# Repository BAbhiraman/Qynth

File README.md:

# DIY Synthesizer using the STM32F407G-DISC1 board
[Working slides](https://docs.google.com/presentation/d/1uzVbpTlb4Z4Ckb4epo5yxM_shybulsgjehzmY5z12NE/edit?usp=sharing)

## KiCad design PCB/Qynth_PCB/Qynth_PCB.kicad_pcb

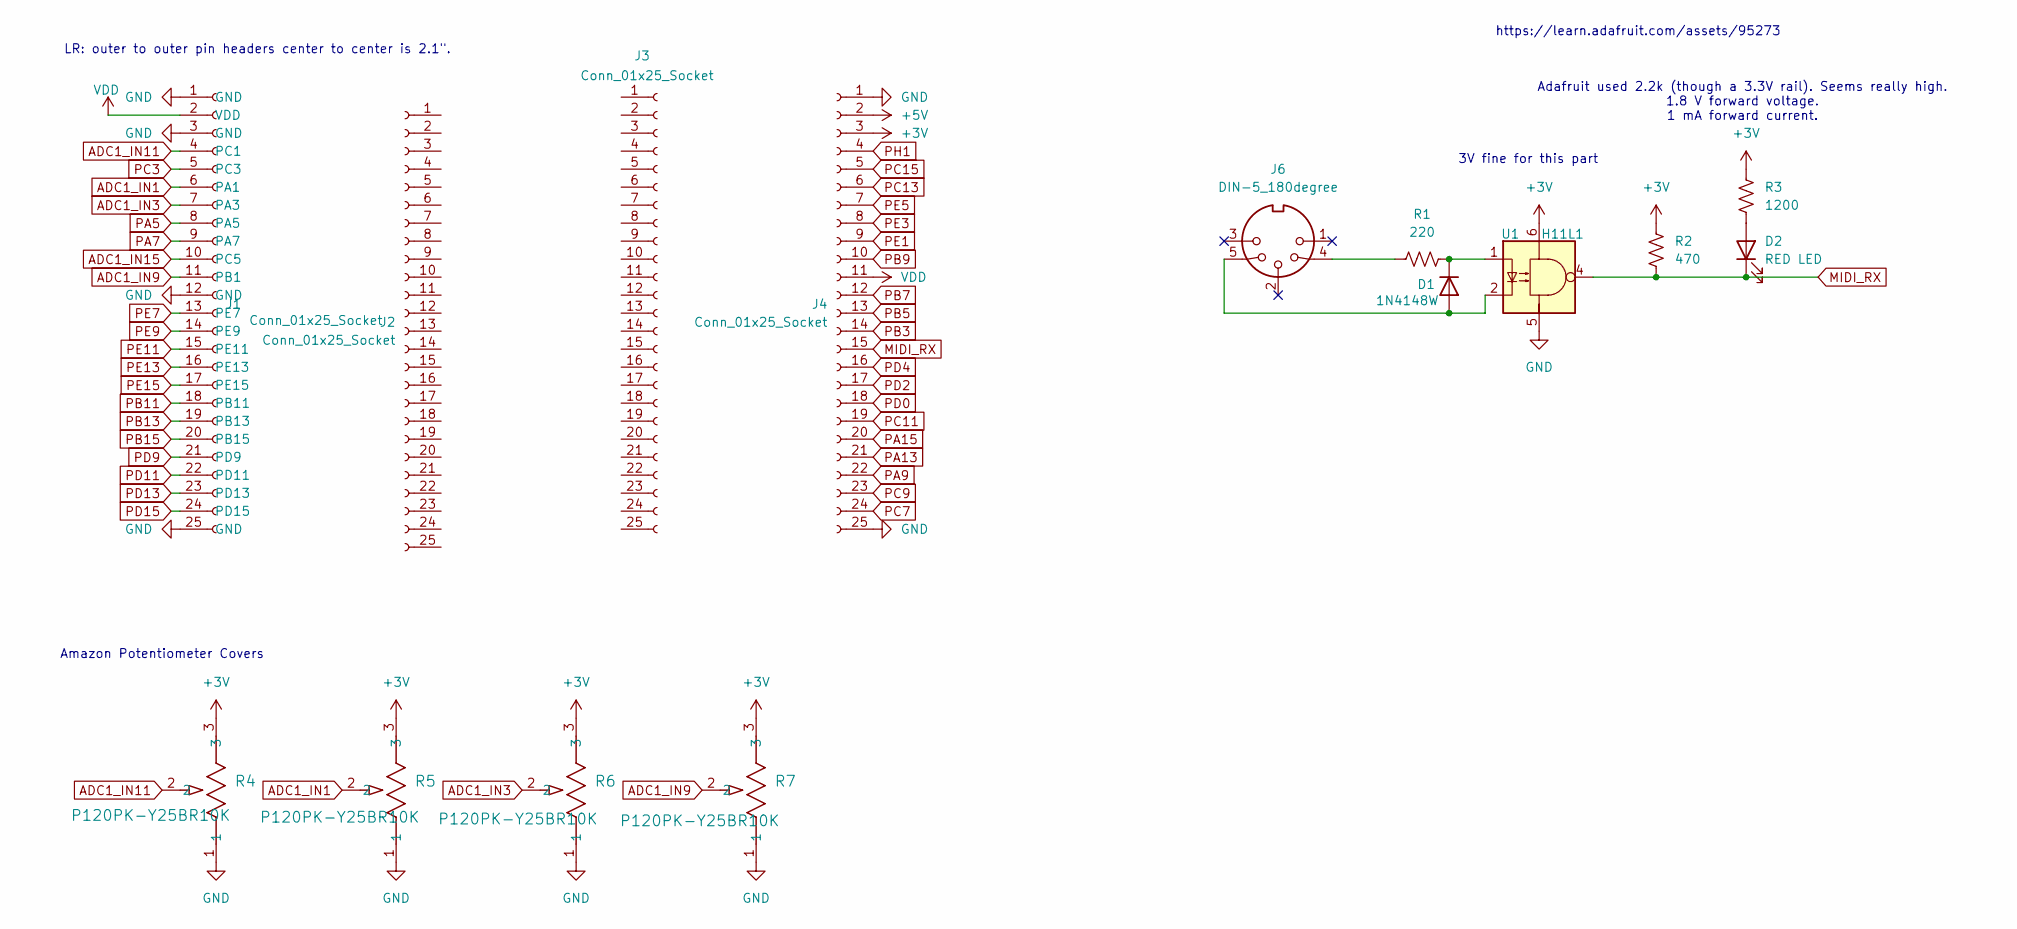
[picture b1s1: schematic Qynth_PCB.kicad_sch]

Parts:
D1: 1N4148W; D_SOD-123
D2: RED LED; LED_0402_1005Metric
J1, J2, J3, J4: Conn_01x25_Socket; PinSocket_1x25_P2.54mm_Vertical
J6: DIN-5_180degree; CUI_SDS-50J
R1: 220; R_0805_2012Metric_Pad1.20x1.40mm_HandSolder
R2: 470; R_0805_2012Metric
R3: 1200; R_0805_2012Metric
R4, R5, R6, R7: P120PK-Y25BR10K; POT_P120PK-x25_TTE
U1: H11L1; SMDIP-6_W7.62mm

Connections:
+3V: J4.3 (3V), R2.2, R3.2, R4.3, R5.3, R6.3, R7.3, U1.6
+5V: J4.2 (5V)
ADC1_IN1: J1.6 (PA1), R5.2
ADC1_IN3: J1.7 (PA3), R6.2
ADC1_IN9: J1.11 (PB1), R7.2
ADC1_IN11: J1.4 (PC1), R4.2
ADC1_IN15: J1.10 (PC5)
GND: J1.1 (GND), J1.3 (GND), J1.12 (GND), J1.25 (GND), J4.1 (GND), J4.25 (GND), R4.1, R5.1, R6.1, R7.1, U1.5
MIDI_RX: D2.1 (K), J4.15 (MIDI_RX), R2.1, U1.4
unnamed: D1.2 (A), J6.5, U1.2
unnamed: D1.1 (K), R1.2, U1.1
unnamed: D2.2 (A), R3.1
unnamed: J6.4, R1.1
PA5: J1.8 (PA5)
PA7: J1.9 (PA7)
PA9: J4.22 (PA9)
PA13: J4.21 (PA13)
PA15: J4.20 (PA15)
PB3: J4.14 (PB3)
PB5: J4.13 (PB5)
PB7: J4.12 (PB7)
PB9: J4.10 (PB9)
PB11: J1.18 (PB11)
PB13: J1.19 (PB13)
PB15: J1.20 (PB15)
PC3: J1.5 (PC3)
PC7: J4.24 (PC7)
PC9: J4.23 (PC9)
PC11: J4.19 (PC11)
PC13: J4.6 (PC13)
PC15: J4.5 (PC15)
PD0: J4.18 (PD0)
PD2: J4.17 (PD2)
PD4: J4.16 (PD4)
PD9: J1.21 (PD9)
PD11: J1.22 (PD11)
PD13: J1.23 (PD13)
PD15: J1.24 (PD15)
PE1: J4.9 (PE1)
PE3: J4.8 (PE3)
PE5: J4.7 (PE5)
PE7: J1.13 (PE7)
PE9: J1.14 (PE9)
PE11: J1.15 (PE11)
PE13: J1.16 (PE13)
PE15: J1.17 (PE15)
PH1: J4.4 (PH1)
VDD: J1.2 (VDD), J4.11 (VDD)

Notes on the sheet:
Amazon Potentiometer Covers
LR: outer to outer pin headers center to center is 2.1".
https://learn.adafruit.com/assets/95273
3V fine for this part
Adafruit used 2.2k (though a 3.3V rail). Seems really high. 1.8 V forward voltage. 1 mA forward current.

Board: 2 copper layers, 15 parts (0 on the bottom side), 12 nets, no tracks yet.

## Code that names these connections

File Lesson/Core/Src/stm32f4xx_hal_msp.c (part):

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    __HAL_RCC_GPIOA_CLK_ENABLE();
    __HAL_RCC_GPIOB_CLK_ENABLE();
    /**ADC1 GPIO Configuration
    PC1     ------> ADC1_IN11
    PC2     ------> ADC1_IN12
    PA1     ------> ADC1_IN1
    PA3     ------> ADC1_IN3
    PC4     ------> ADC1_IN14
    PB0     ------> ADC1_IN8
    PB1     ------> ADC1_IN9
    */
    GPIO_InitStruct.Pin = GPIO_PIN_1|GPIO_PIN_2|GPIO_PIN_4;
    GPIO_InitStruct.Mode = GPIO_MODE_ANALOG;
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    __HAL_RCC_ADC1_CLK_DISABLE();

    /**ADC1 GPIO Configuration
    PC1     ------> ADC1_IN11
    PC2     ------> ADC1_IN12
    PA1     ------> ADC1_IN1
    PA3     ------> ADC1_IN3
    PC4     ------> ADC1_IN14
    PB0     ------> ADC1_IN8
    PB1     ------> ADC1_IN9
    */
    HAL_GPIO_DeInit(GPIOC, GPIO_PIN_1|GPIO_PIN_2|GPIO_PIN_4);

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
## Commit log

2025-03-21 got ping from ext DAC
2025-03-22 heard some sound!
2025-03-22 DMA I2S working but clicking persists
2025-03-22 what the fuck? kinda cool though.
2025-03-22 ok this doesn't have buzzing, very sensitive though
2025-03-23 working through double buffering issues, ode to joy.
2025-03-23 fixed volatile thing by using loop variable. Keep an eye on this issue.
2025-03-23 MAJOR DAJOR progress.
    Got rid of clicking artifacts. Ctrler spent all its time calculating sine and barely finished on time. New logic uses sine lookup table.
    TODO put flag logic back to previous state.
2025-03-27 restoring old double buffering logic. prototyping serial over USB.
2025-04-02 got midi_input_test to compile with files from internet
2025-04-02 Made substitutions recommended by hackaday.io. Compiled.
2025-04-04 MIDI_Input_test_youtube (name not true) compiles with changes from Dekrispator
    minor modification to USB_HOST/App/usb_host.c for includes. This will despawn when running .ioc.
2025-04-04 MX_USB_HOST_Process not freezing, things building, still not triggering LED upon keypress
2025-04-04 ditto last commit but minus some typos
2025-04-04 another checkpoint, still doesn't work, but it runs
2025-05-23 waveform working, debugging decay cutoff
2025-05-23 IT WORKS BABY
2025-05-23 note datastructure and ADR envelope working nice!
2025-06-03 ADR envelope based on potentiometers
2025-06-03 harmony has landed baby
2025-06-06 Useful MIDI parsing tool
2025-06-06 minimalist sine synth with MIDI input working, though pretty buggy
2025-06-07 fixed MIDI state bugs, no latency or input errors now. Pedal won't work, forget it.
2025-06-07 active notes logic needs work
2025-06-07 sweet sweet polyphony!!!
2025-06-07 decay working! sounding really good
2025-06-07 refactoring, commenting.
2025-06-08 push button to switch sounds
2025-06-09 got rid of some division, added some waveforms
2025-06-22 checkpoint before adding cmsis iir
2025-06-28 stm32: lowpass filters. PCB: Kicad files started.
2025-07-06 compressor coded but takes too much compute. legato working.
2025-07-06 C compiler optimizations, speed improvements.
2025-07-09 Most buttons and LEDs working, knobs mapped.
2025-07-11 implemented doodle mode functionality, added new waveforms
2025-07-11 Attempted arpeggio implementation; untested
2025-07-12 snake case grammar
2025-07-24 arpeggio mode works. sometimes drops notes though
2025-07-26 vibrato mode working for legato
2025-07-26 multi voice vibrato working!
2025-07-28 legato mode rips now (knob implemented)
2025-07-29 Turning a knob in a preset works
2025-07-29 fixed hammond amplitude
2025-08-01 changed LPF to log spacing - way better.
2025-08-05 added LPmod, vulnerable to pops in legato mode
2025-08-06 doodle mode upon startup starts in quiet mode
2025-08-08 thank god this works with a Nord now so those with a $5000 synth can ignore it
2025-08-08 stereo baby!
2025-08-27 Modifying MIDI state machine to work w Yamaha again
2025-09-20 pre henry commit
2025-12-05 files for stm32 synth lesson
2026-01-26 Increased sample rate to 48 kHz using more efficient compilation. Some new features for Aimee.

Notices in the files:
Lesson/Core/Src/stm32f4xx_hal_msp.c:
Copyright (c) 2025 STMicroelectronics.
All rights reserved.
This software is licensed under terms that can be found in the LICENSE file
